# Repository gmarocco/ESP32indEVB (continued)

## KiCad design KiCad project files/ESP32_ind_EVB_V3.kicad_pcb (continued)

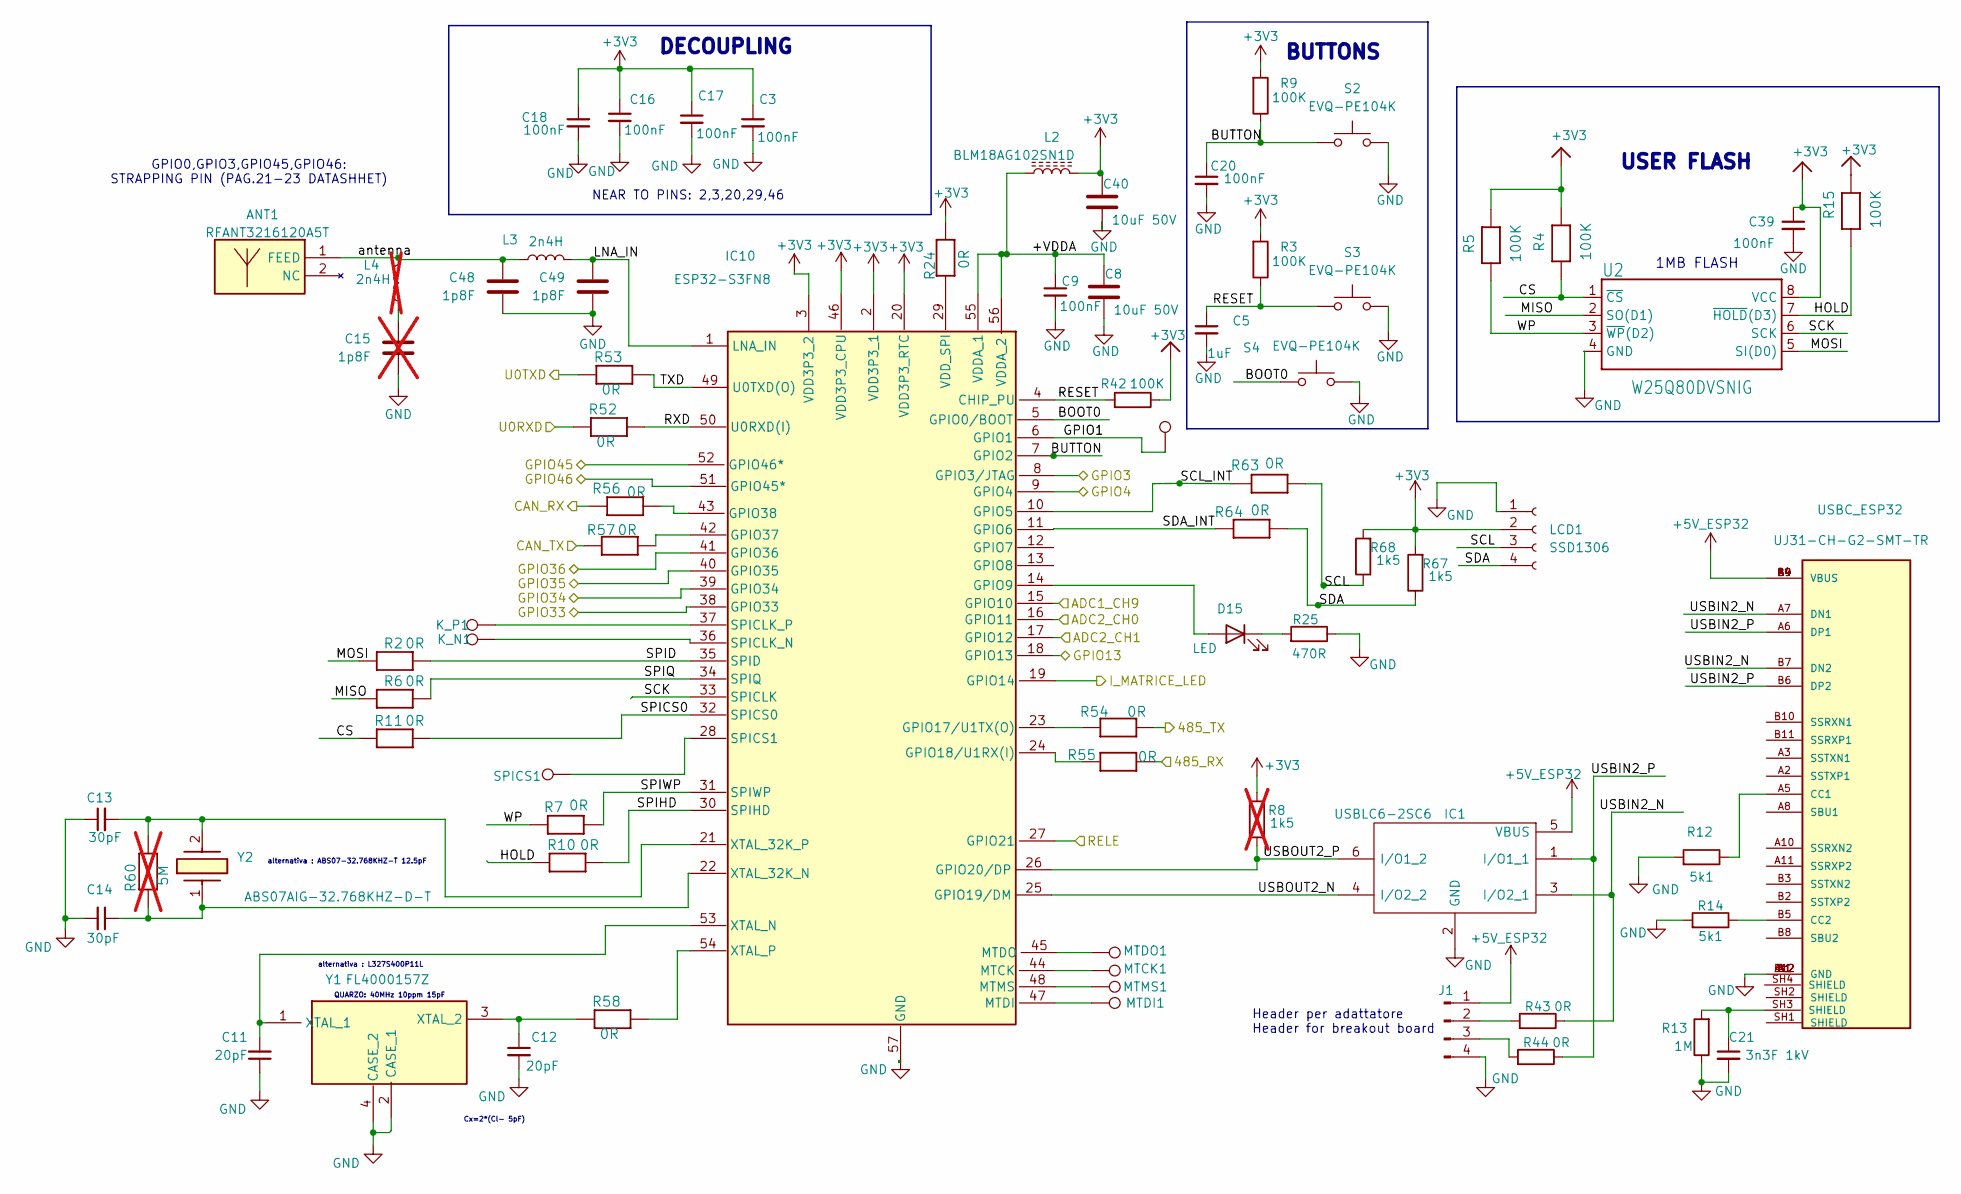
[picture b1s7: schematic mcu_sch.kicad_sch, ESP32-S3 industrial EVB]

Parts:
ANT1: RFANT3216120A5T; ANTC3216X130N; Mouser Part Number 791-RFANT3216120A5T
C3, C9, C16, C17, C18, C20, C39: 100nF; C_0603_1608Metric_Pad1.08x0.95mm_HandSolder
C5: 1uF; C_0603_1608Metric_Pad1.08x0.95mm_HandSolder
C8, C40: 10uF 50V; C_1206_3216Metric_Pad1.33x1.80mm_HandSolder
C11, C12: 20pF; C_0603_1608Metric_Pad1.08x0.95mm_HandSolder
C13, C14: 30pF; C_0603_1608Metric_Pad1.08x0.95mm_HandSolder
C15: 1p8F; C_0603_1608Metric_Pad1.08x0.95mm_HandSolder; not fitted
C21: 3n3F 1kV; C_1206_3216Metric_Pad1.33x1.80mm_HandSolder
C48, C49: 1p8F; C_0603_1608Metric_Pad1.08x0.95mm_HandSolder
D15: LED; LED_0603_1608Metric_Pad1.05x0.95mm_HandSolder
IC1: USBLC6-2SC6; SOT23-6; Mouser Part Number 511-USBLC6-2SC6
IC10: ESP32-S3FN8; QFN40P700X700X90-57N-D; Mouser Part Number 356-ESP32-S3FN8
J1: Conn_01x04_Pin; PinHeader_1x04_P2.54mm_Vertical
K_N1: TestPoint; TestPoint_THTPad_D1.0mm_Drill0.5mm
K_P1: TestPoint; TestPoint_THTPad_D1.0mm_Drill0.5mm
L2: BLM18AG102SN1D; L_0603_1608Metric_Pad1.05x0.95mm_HandSolder
L3: 2n4H; L_0603_1608Metric
L4: 2n4H; L_0603_1608Metric; not fitted
LCD1: SSD1306; PinHeader_1x04_P2.54mm_Vertical
MTCK1: TestPoint; TestPoint_THTPad_D1.0mm_Drill0.5mm
MTDI1: TestPoint; TestPoint_THTPad_D1.0mm_Drill0.5mm
MTDO1: TestPoint; TestPoint_THTPad_D1.0mm_Drill0.5mm
MTMS1: TestPoint; TestPoint_THTPad_D1.0mm_Drill0.5mm
R2, R6, R7, R10, R11, R24, R43, R44, R52, R53, R54, R55, R56, R57, R58, R63, R64: 0R; R_0603_1608Metric_Pad0.98x0.95mm_HandSolder
R3, R4, R5, R9, R15, R42: 100K; R_0603_1608Metric_Pad0.98x0.95mm_HandSolder
R8: 1k5; R_0603_1608Metric_Pad0.98x0.95mm_HandSolder; not fitted
R12, R14: 5k1; R_0603_1608Metric_Pad0.98x0.95mm_HandSolder
R13: 1M; R_0603_1608Metric_Pad0.98x0.95mm_HandSolder
R25: 470R; R_0603_1608Metric_Pad0.98x0.95mm_HandSolder
R60: 5M; R_0603_1608Metric_Pad0.98x0.95mm_HandSolder; not fitted
R67, R68: 1k5; R_0603_1608Metric_Pad0.98x0.95mm_HandSolder
S2, S3, S4: EVQ-PE104K; EVQPE104K; Mouser Part Number 667-EVQ-PE104K
SPICS1: TestPoint; TestPoint_THTPad_D1.0mm_Drill0.5mm
TP72: TestPoint; TestPoint_Pad_through hole 1.5mm
U2: W25Q80DVSNIG; SOIC-8_3.9x4.9mm_P1.27mm
USBC_ESP32: UJ31-CH-G2-SMT-TR; UJ31CHG2SMTTR; PART_REV 1.01
Y1: FL4000157Z; Mouser Part Number 729-FL4000157Z
Y2: ABS07AIG-32.768KHZ-D-T; ABS07AIG; Mouser Part Number 815-S07AIG-32.768-DT

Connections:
+3V3: C3.1, C16.1, C17.1, C18.1, C39.1, C40.1, IC10.2 (VDD3P3_1), IC10.3 (VDD3P3_2), IC10.20 (VDD3P3_RTC), IC10.46 (VDD3P3_CPU), L2.2, LCD1.2, R3.2, R4.2, R5.2, R8.2, R9.2, R15.2, R24.1, R42.1, R67.2, R68.2, U2.8 (VCC); also elsewhere on the board
+5V_ESP32: IC1.5 (VBUS), J1.1, USBC_ESP32.A4 (VBUS), USBC_ESP32.A9 (VBUS), USBC_ESP32.B4 (VBUS), USBC_ESP32.B9 (VBUS); also elsewhere on the board
/gerarchico Sheet/ESP32-S3 MCU/485_RX: R55.1; also elsewhere on the board
/gerarchico Sheet/ESP32-S3 MCU/485_TX: R54.1; also elsewhere on the board
/gerarchico Sheet/ESP32-S3 MCU/+VDDA: C8.1, C9.1, IC10.55 (VDDA_1), IC10.56 (VDDA_2), L2.1
/gerarchico Sheet/ESP32-S3 MCU/ADC1_CH9: IC10.15 (GPIO10); also elsewhere on the board
/gerarchico Sheet/ESP32-S3 MCU/ADC2_CH0: IC10.16 (GPIO11); also elsewhere on the board
/gerarchico Sheet/ESP32-S3 MCU/ADC2_CH1: IC10.17 (GPIO12); also elsewhere on the board
/gerarchico Sheet/ESP32-S3 MCU/BOOT0: IC10.5 (GPIO0/BOOT), S4.1
/gerarchico Sheet/ESP32-S3 MCU/BUTTON: C20.1, IC10.7 (GPIO2), R9.1, S2.1
/gerarchico Sheet/ESP32-S3 MCU/CAN_RX: R56.2; also elsewhere on the board
/gerarchico Sheet/ESP32-S3 MCU/CAN_TX: R57.2; also elsewhere on the board
/gerarchico Sheet/ESP32-S3 MCU/CS: R4.1, R11.2, U2.1 (~CS)
/gerarchico Sheet/ESP32-S3 MCU/GPIO1: IC10.6 (GPIO1), TP72.1
/gerarchico Sheet/ESP32-S3 MCU/GPIO3: IC10.8 (GPIO3/JTAG); also elsewhere on the board
/gerarchico Sheet/ESP32-S3 MCU/GPIO4: IC10.9 (GPIO4); also elsewhere on the board
/gerarchico Sheet/ESP32-S3 MCU/GPIO13: IC10.18 (GPIO13); also elsewhere on the board
/gerarchico Sheet/ESP32-S3 MCU/GPIO33: IC10.38 (GPIO33); also elsewhere on the board
/gerarchico Sheet/ESP32-S3 MCU/GPIO34: IC10.39 (GPIO34); also elsewhere on the board
/gerarchico Sheet/ESP32-S3 MCU/GPIO35: IC10.40 (GPIO35); also elsewhere on the board
/gerarchico Sheet/ESP32-S3 MCU/GPIO36: IC10.41 (GPIO36); also elsewhere on the board
/gerarchico Sheet/ESP32-S3 MCU/GPIO45: IC10.52 (GPIO46*); also elsewhere on the board
/gerarchico Sheet/ESP32-S3 MCU/GPIO46: IC10.51 (GPIO45*); also elsewhere on the board
/gerarchico Sheet/ESP32-S3 MCU/HOLD: R10.2, R15.1, U2.7 (~HOLD(D3))
/gerarchico Sheet/ESP32-S3 MCU/I_MATRICE_LED: IC10.19 (GPIO14); also elsewhere on the board
/gerarchico Sheet/ESP32-S3 MCU/LNA_IN: C49.1, IC10.1 (LNA_IN), L3.1
/gerarchico Sheet/ESP32-S3 MCU/MISO: R6.2, U2.2 (SO(D1))
/gerarchico Sheet/ESP32-S3 MCU/MOSI: R2.2, U2.5 (SI(D0))
/gerarchico Sheet/ESP32-S3 MCU/RELE: IC10.27 (GPIO21); also elsewhere on the board
/gerarchico Sheet/ESP32-S3 MCU/RESET: C5.1, IC10.4 (CHIP_PU), R3.1, R42.2, S3.1
/gerarchico Sheet/ESP32-S3 MCU/RXD: IC10.50 (U0RXD(I)), R52.1
/gerarchico Sheet/ESP32-S3 MCU/SCK: IC10.33 (SPICLK), U2.6 (SCK)
/gerarchico Sheet/ESP32-S3 MCU/SCL: LCD1.3, R63.2, R68.1
/gerarchico Sheet/ESP32-S3 MCU/SCL_INT: IC10.10 (GPIO5), R63.1
/gerarchico Sheet/ESP32-S3 MCU/SDA: LCD1.4, R64.2, R67.1
/gerarchico Sheet/ESP32-S3 MCU/SDA_INT: IC10.11 (GPIO6), R64.1
/gerarchico Sheet/ESP32-S3 MCU/SPICS0: IC10.32 (SPICS0), R11.1
/gerarchico Sheet/ESP32-S3 MCU/SPID: IC10.35 (SPID), R2.1
/gerarchico Sheet/ESP32-S3 MCU/SPIHD: IC10.30 (SPIHD), R10.1
/gerarchico Sheet/ESP32-S3 MCU/SPIQ: IC10.34 (SPIQ), R6.1
/gerarchico Sheet/ESP32-S3 MCU/SPIWP: IC10.31 (SPIWP), R7.1
/gerarchico Sheet/ESP32-S3 MCU/TXD: IC10.49 (U0TXD(O)), R53.1
/gerarchico Sheet/ESP32-S3 MCU/U0RXD: R52.2; also elsewhere on the board
/gerarchico Sheet/ESP32-S3 MCU/U0TXD: R53.2; also elsewhere on the board
/gerarchico Sheet/ESP32-S3 MCU/USBIN2_N: IC1.3 (I/O2_1), R43.1, USBC_ESP32.A7 (DN1), USBC_ESP32.B7 (DN2)
/gerarchico Sheet/ESP32-S3 MCU/USBIN2_P: IC1.1 (I/O1_1), R44.1, USBC_ESP32.A6 (DP1), USBC_ESP32.B6 (DP2)
/gerarchico Sheet/ESP32-S3 MCU/USBOUT2_N: IC1.4 (I/O2_2), IC10.25 (GPIO19/DM)
/gerarchico Sheet/ESP32-S3 MCU/USBOUT2_P: IC1.6 (I/O1_2), IC10.26 (GPIO20/DP), R8.1
/gerarchico Sheet/ESP32-S3 MCU/WP: R5.1, R7.2, U2.3 (~WP(D2))
/gerarchico Sheet/ESP32-S3 MCU/antenna: ANT1.1 (FEED), C48.1, L3.2, L4.1
GND: C3.2, C5.2, C8.2, C9.2, C11.1, C12.2, C13.1, C14.2, C15.2, C16.2, C17.2, C18.2, C20.2, C21.2, C39.2, C40.2, C48.2, C49.2, IC1.2 (GND), IC10.57 (GND), J1.4, LCD1.1, R12.2, R13.1, R14.2, R25.1, S2.2, S3.2, S4.2, U2.4 (GND), USBC_ESP32.A1 (GND), USBC_ESP32.A12 (GND), USBC_ESP32.B1 (GND), USBC_ESP32.B12 (GND), Y1.2 (CASE_1), Y1.4 (CASE_2); also elsewhere on the board
unnamed: C15.1, L4.2
unnamed: C21.1, R13.2, USBC_ESP32.SH3 (SHIELD)
unnamed: D15.2 (A), IC10.14 (GPIO9)
unnamed: D15.1 (K), R25.2
unnamed: IC10.23 (GPIO17/U1TX(O)), R54.2
unnamed: IC10.24 (GPIO18/U1RX(I)), R55.2
unnamed: IC10.42 (GPIO37), R57.1
unnamed: IC10.43 (GPIO38), R56.1
unnamed: IC10.44 (MTCK), MTCK1.1
unnamed: IC10.47 (MTDI), MTDI1.1
unnamed: IC10.45 (MTDO), MTDO1.1
unnamed: IC10.48 (MTMS), MTMS1.1
unnamed: IC10.36 (SPICLK_N), K_N1.1
unnamed: IC10.37 (SPICLK_P), K_P1.1
unnamed: IC10.28 (SPICS1), SPICS1.1
unnamed: IC10.29 (VDD_SPI), R24.2
unnamed: C14.1, IC10.22 (XTAL_32K_N), R60.2, Y2.1
unnamed: C13.2, IC10.21 (XTAL_32K_P), R60.1, Y2.2
unnamed: C11.2, IC10.53 (XTAL_N), Y1.1 (XTAL_1)
unnamed: IC10.54 (XTAL_P), R58.1
unnamed: J1.2, R43.2
unnamed: J1.3, R44.2
unnamed: R12.1, USBC_ESP32.A5 (CC1)
unnamed: R14.1, USBC_ESP32.B5 (CC2)
unnamed: C12.1, R58.2, Y1.3 (XTAL_2)

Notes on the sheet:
USER FLASH
GPIO0,GPIO3,GPIO45,GPIO46: STRAPPING PIN (PAG.21-23 DATASHHET)
1MB FLASH
NEAR TO PINS: 2,3,20,29,46
BUTTONS
Header per adattatore Header for breakout board
QUARZO: 40MHz 10ppm 15pF
alternativa : L327S400P11L
Cx=2*(Cl- 5pF)
alternativa : ABS07-32.768KHZ-T 12.5pF
DECOUPLING

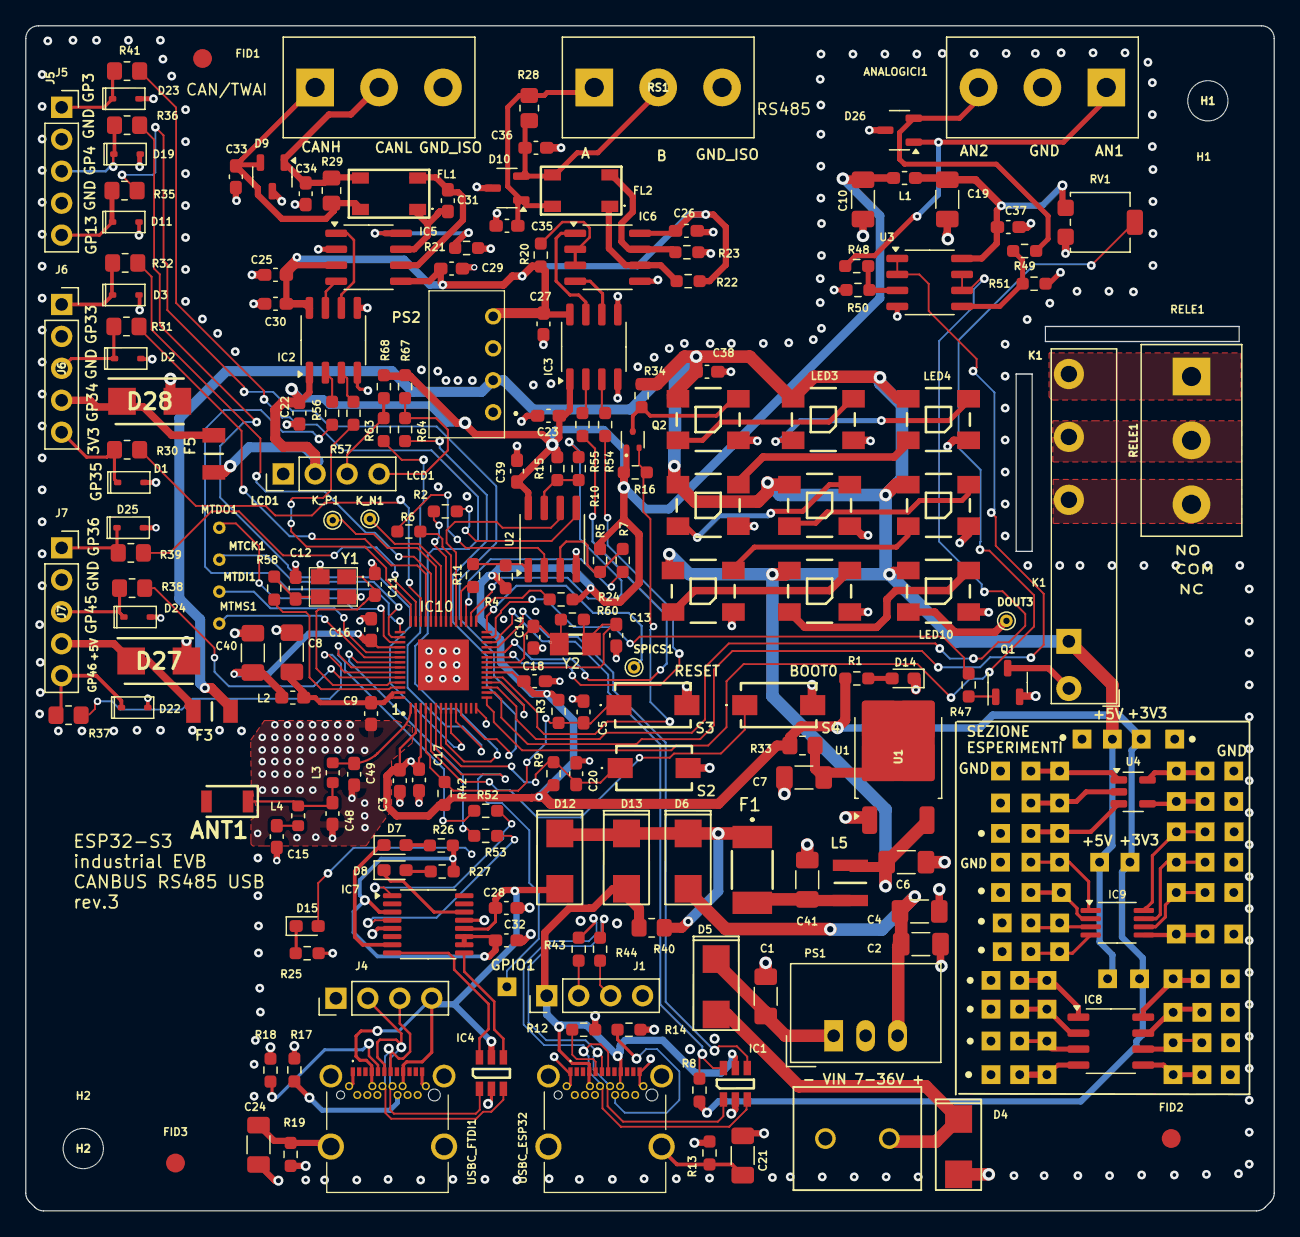
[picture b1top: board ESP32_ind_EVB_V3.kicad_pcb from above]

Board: 4 copper layers, 99.2 x 94.2 mm, 270 parts (0 on the bottom side), 165 nets.

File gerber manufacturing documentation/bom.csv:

Designator,Footprint,Quantity,Value,LCSC Part #
"ANALOGICI1, CAN1, RELE1, RS1",TerminalBlock_bornier-3_P5.08mm,4,282837-3,
ANT1,ANTC3216X130N,1,RFANT3216120A5T,
"C1, C2, C4",1206,3,10uF_50V,
"C10, C19, C40, C41, C6, C7, C8",1206,7,10uF 50V,
"C11, C12",0603,2,20pF,
"C13, C14",0603,2,30pF,
"C15, C48, C49",0603,3,1p8F,
"C16, C17, C18, C20, C22, C23, C25, C26, C27, C28, C29, C3, C30, C32, C37, C38, C39, C9",0603,18,100nF,
"C21, C24",1206,2,3n3F 1kV,
"C31, C33, C34, C35, C36",0603,5,100PF,
C5,0603,1,1uF,
"D1, D11, D19, D2, D22, D23, D24, D25, D3",SOD-323,9,ESD7351HT1G,
"D10, D26, D9",SOT-23-3,3,PESD2CANFD27L-TR,
"D12, D13, D5, D6",SMA,4,CDBA340-HF,
"D14, D15, D7, D8",0603,4,LED,
D27,DIOM5436X244N,1,SMBJ5.0A,
D28,DIOM5436X244N,1,SMBJ3V3-E3/5B,
D4,DIOM5436X261N,1,SMBJ36CA,
"DOUT3, K_N1, K_P1, MTCK1, MTDI1, MTDO1, MTMS1, SPICS1",TestPoint_THTPad_D1.0mm_Drill0.5mm,8,TestPoint,
EXT_POWER1,2828372,1,282837-2,
F1,1812L010DR,1,1812L150_24MR,
"F3, F5",1206L05015YR,2,1206L050_15YR,
"FID1, FID2, FID3",Fiducial_1.5mm_Mask3mm,3,Fiducial,
"FL1, FL2",ACT45B1012PTL003,2,ACT45B-101-2P-TL003,
"H1, H2",MountingHole_3.2mm_M3,2,MountingHole,
"IC1, IC4",SOT23-6,2,USBLC6-2SC6,
IC10,QFN40P700X700X90-57N-D,1,ESP32-S3FN8,
"IC2, IC3",SO-8_3.9x4.9mm_P1.27mm,2,ADUM3201ARZ-RL7,
IC5,SO-8_3.9x4.9mm_P1.27mm,1,MCP2562-E_SN,
IC6,SO-8_3.9x4.9mm_P1.27mm,1,MAX13488EESA+T,
IC7,TSSOP-16_4.4x5mm_P0.65mm,1,FT230XS-R,
IC8,SO-8_3.9x4.9mm_P1.27mm,1,NE555DR,
IC9,MSOP-8_3x3mm_P0.65mm,1,NE555DR,
"J1, J4",PinHeader_1x04_P2.54mm_Vertical,2,Conn_01x04_Pin,
"J5, J6, J7",PinSocket_1x05_P2.54mm_Vertical,3,Conn_01x05_Socket,
K1,Relay_SPDT_Finder_34.51_Vertical,1,FINDER-34.51,
"L1, L2",0603,2,BLM18AG102SN1D,
"L3, L4",0603,2,2n4H,
L5,1277ASH100MP2,1,DFE322512F-4R7M=P2,
LCD1,PinHeader_1x04_P2.54mm_Vertical,1,SSD1306,
"LED10, LED2, LED3, LED4, LED5, LED6, LED7, LED8, LED9",WS2812B,9,WS2812B,
PS1,Converter_DCDC_TRACO_TSR-1_THT,1,TSR_1-2450,
PS2,TEA10505,1,TEA_1-0505,
Q1,SOT-23-3,1,DRDC3105F-7,
Q2,SOT-523,1,DMG1012T,
"R1, R20, R22, R23",0603,4,1K,
"R10, R11, R2, R24, R43, R44, R47, R52, R53, R54, R55, R56, R57, R58, R6, R63, R64, R7",0603,18,0R,
"R12, R14, R17, R18",0603,4,5k1,
"R13, R19",0603,2,1M,
"R15, R3, R4, R42, R5, R9",0603,6,100K,
R16,0603,1,2k2,
"R21, R25, R26, R27",0603,4,470R,
"R28, R29",0805,2,120R,
"R30, R31, R32, R35, R36, R37, R38, R39, R41",0805,9,49R9,
"R33, R40",0805,2,0R 0.5W 0805,
"R34, R50, R51",0603,3,4k7,
"R48, R49",0603,2,47k,
R60,0603,1,5M,
"R67, R68, R8",0603,3,1k5,
RV1,Potentiometer_Bourns_3314G_Vertical,1,10k,
"S2, S3, S4",EVQPE104K,3,EVQ-PE104K,
"TP1, TP10, TP11, TP12, TP13, TP14, TP15, TP16, TP17, TP18, TP19, TP2, TP20, TP21, TP22, TP23, TP24, TP25, TP26, TP27, TP28, TP29, TP3, TP30, TP31, TP32, TP33, TP34, TP35, TP36, TP37, TP38, TP39, TP4, TP40, TP41, TP42, TP43, TP44, TP45, TP46, TP47, TP48, TP49, TP5, TP50, TP51, TP52, TP53, TP54, TP55, TP56, TP57, TP58, TP59, TP6, TP60, TP61, TP62, TP63, TP64, TP65, TP66, TP67, TP68, TP69, TP7, TP70, TP71, TP72, TP8, TP9",TestPoint_Pad_through hole 1.5mm,72,TestPoint,
U1,TO-252-2,1,NCP1117-3.3_TO252,
U2,SOIC-8_3.9x4.9mm_P1.27mm,1,W25Q80DVSNIG,
U3,SO-8_3.9x4.9mm_P1.27mm,1,LMV358IDR,
U4,SOT-23-5,1,NCP718xSN180,
"USBC_ESP32, USBC_FTDI1",UJ31CHG2SMTTR,2,UJ31-CH-G2-SMT-TR,
Y1,FL4000157Z,1,FL4000157Z,
Y2,ABS07AIG,1,ABS07AIG-32.768KHZ-D-T,

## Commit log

2025-06-01 Create kicad project files
2026-01-09 Add files via upload
    This is an intercative view of the board
